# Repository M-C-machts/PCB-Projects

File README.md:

# PCB-Projects
My Personal PCB Projects

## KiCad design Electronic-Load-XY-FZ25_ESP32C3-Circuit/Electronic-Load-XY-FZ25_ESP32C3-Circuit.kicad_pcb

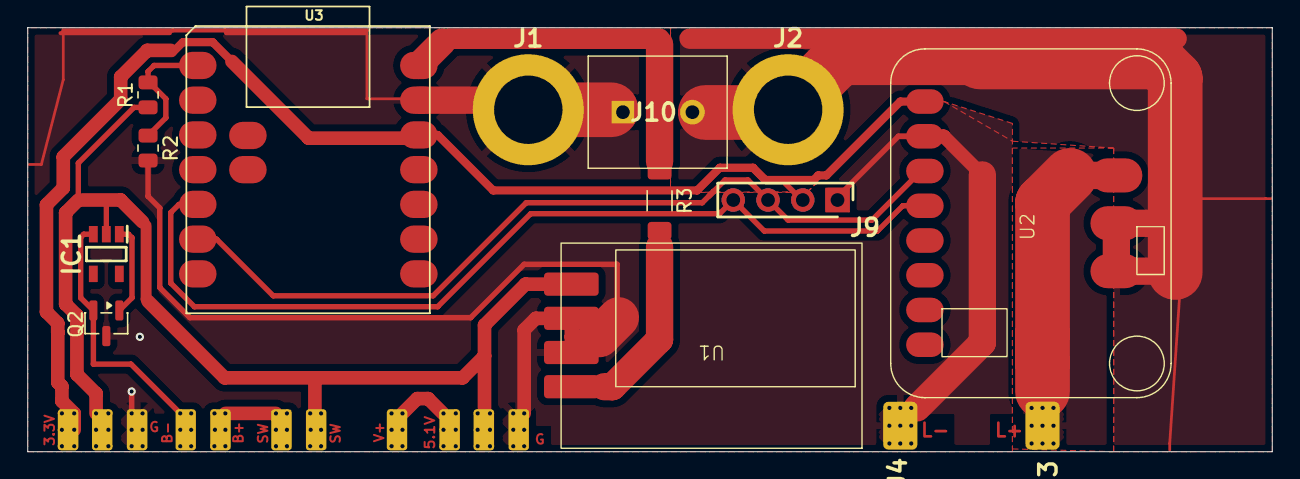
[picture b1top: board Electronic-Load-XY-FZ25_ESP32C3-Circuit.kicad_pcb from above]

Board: 2 copper layers, 91.0 x 31.0 mm, 19 parts (0 on the bottom side), 14 nets.

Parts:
3.3V, 5.1V: Conn_1x3_PH; Mechc.-solder-pad_1x3
B+: Conn_1x2_PH; Mechc.-solder-pad_1x2
IC1: BD5330G; SOT95P280X125-5M
J1, J2: Banana-Socket; banana-socket
J3, J4: mech.-solder-pad_large; Mechc.-solder-pad-large
J8: mech.-solder-pad; Mechc.-solder-pad
J9: Conn_1x4_PH; Conn_1x4_PH_drill dot
J10: Conn_Terminal-Block_1x2
Q2: AO3416; SOT-23
R1, R2: 220k; R_0805_2012Metric
R3: 0R; R_1206_3216Metric_Pad1.30x1.75mm_HandSolder
SW: Conn_1x2_PH; Mechc.-solder-pad_1x2
U1: LiPO-Charge; TP5000-Charge-IC_smal-led
U2: Adafruit INA228; INA228-Footprint
U3: XIAO-ESP32C3; MOUDLE14P-SMD-2.54-21X17.8MM

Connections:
+3.3V: 3.3V.3 (3.3V_out), J9.2 (VDD), U2.1 (VIN), U3.12 (3V3)
+5V: R3.2, U1.1 (IN+)
Banana+: J2.1, J10.2, U2.9 (Vin+), U2.10 (VBus)
GND: 3.3V.1 (GND), 5.1V.1 (GND), J1.1, J4.1, J9.1 (GND), J10.1, Q2.3 (D), R2.2, U1.2 (GND), U1.3 (GND), U2.2 (GND), U3.13 (GND)
L+: J3.1, U2.11 (Vin-)
unnamed: B+.1 (B-), IC1.3 (GND), Q2.2 (S)
unnamed: IC1.1 (VOUT), Q2.1 (G)
unnamed: B+.2 (B+), SW.1
unnamed: 5.1V.3 (5.1V_out), J8.1
unnamed: J9.3 (SCK), U2.3 (SCL), U3.6 (PA9_A5_D5_SCL)
unnamed: J9.4 (SDA), U2.4 (SDA), U3.5 (PA8_A4_D4_SDA)
unnamed: R3.1, U3.14 (5V)
unnamed: R1.2, R2.1, U3.1 (PA02_A0_D0)
V-BATT+: 3.3V.2 (Vbatt), 5.1V.2 (Vbatt), IC1.2 (VDD), R1.1, SW.2, U1.4 (B+)

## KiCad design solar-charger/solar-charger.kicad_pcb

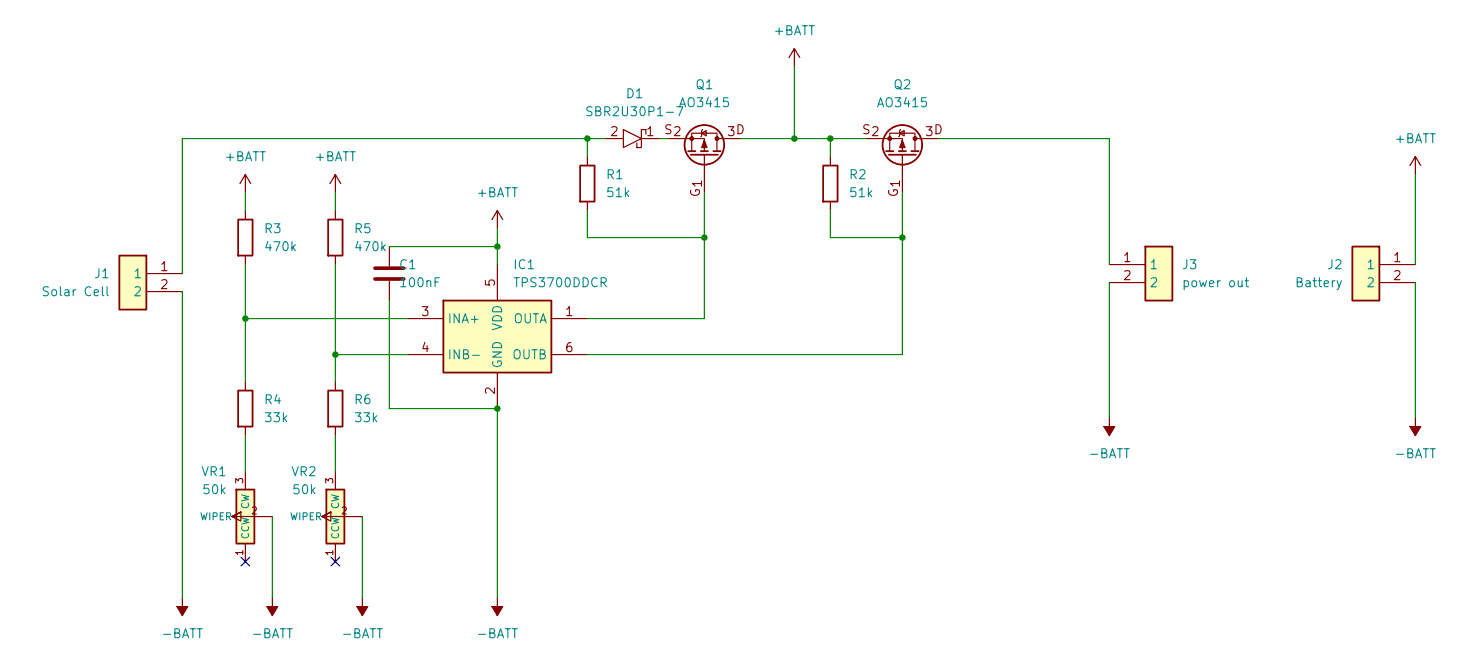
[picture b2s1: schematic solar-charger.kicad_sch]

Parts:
C1: 100nF; C_0805_2012Metric_Pad1.18x1.45mm_HandSolder
D1: SBR2U30P1-7; SODFL3718X100N; Mouser Part Number 621-SBR2U30P1-7
IC1: TPS3700DDCR; SOT98P280X110-6N; Mouser Part Number 595-TPS3700DDCR
J1: Solar Cell; 10129378902001BLF; Manufacturer_Part_Number 10129378-902001BLF
J2: Battery; 10129378902001BLF; Manufacturer_Part_Number 10129378-902001BLF
J3: power out; 10129378902001BLF; Manufacturer_Part_Number 10129378-902001BLF
Q1, Q2: AO3415; SOT-23; Manufacturer_Part_Number AO3415
R1, R2: 51k; R_0805_2012Metric_Pad1.20x1.40mm_HandSolder
R3, R5: 470k; R_0805_2012Metric_Pad1.20x1.40mm_HandSolder
R4, R6: 33k; R_0805_2012Metric_Pad1.20x1.40mm_HandSolder
VR1, VR2: 50k; TC33X2104E; Mouser Part Number 652-TC33X-2-104E

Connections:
+BATT: C1.1, IC1.5 (VDD), J2.1, Q1.3 (D), Q2.2 (S), R2.1, R3.1, R5.1
-BATT: C1.2, IC1.2 (GND), J1.2, J2.2, J3.2, VR1.2 (WIPER), VR2.2 (WIPER)
unnamed: D1.2 (A), J1.1, R1.1
unnamed: D1.1 (K), Q1.2 (S)
unnamed: IC1.3 (INA+), R3.2, R4.1
unnamed: IC1.4 (INB-), R5.2, R6.1
unnamed: IC1.1 (OUTA), Q1.1 (G), R1.2
unnamed: IC1.6 (OUTB), Q2.1 (G), R2.2
unnamed: J3.1, Q2.3 (D)
unnamed: R4.2, VR1.3 (CW)
unnamed: R6.2, VR2.3 (CW)

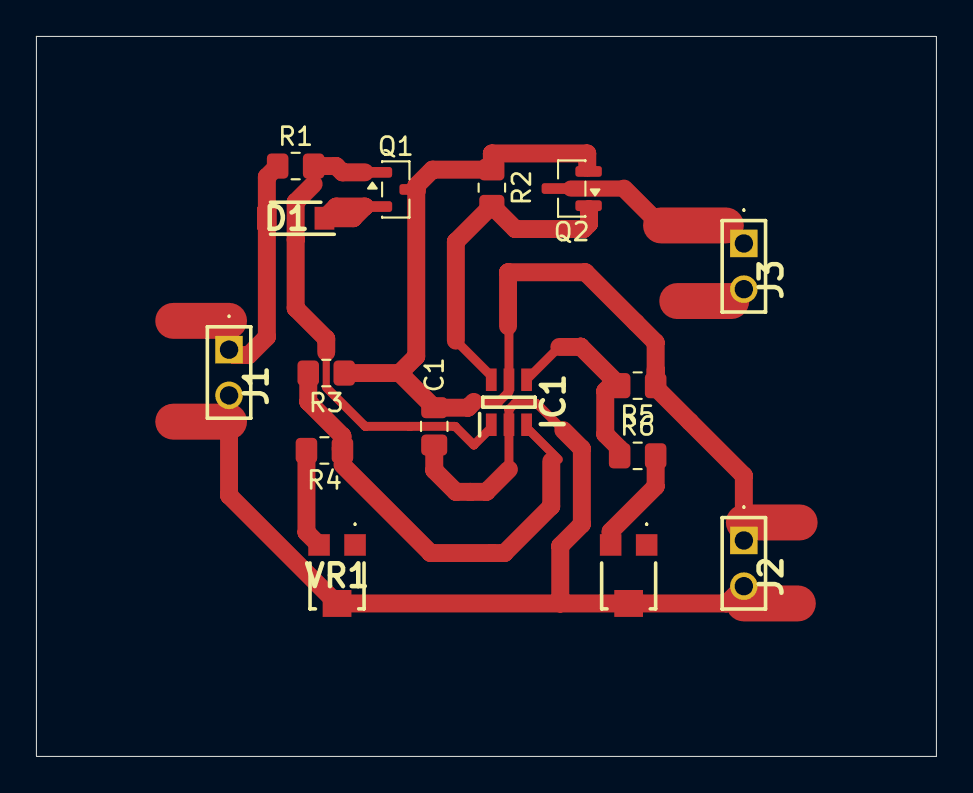
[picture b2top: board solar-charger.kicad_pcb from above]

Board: 2 copper layers, 50.0 x 40.0 mm, 16 parts (0 on the bottom side), 11 nets.

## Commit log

2025-07-22 Add PCB for solar-charger
2025-07-22 Rename
2025-11-21 Add personal part library and update
2025-12-05 Add to part library
2025-12-05 finish 1. working PCB
2025-12-12 Save
2025-12-19 Add working circuit, needs logtime testing
2026-01-20 Add new ICs etc.
2026-01-20 Add first Circuit
2026-01-23 Add, rework parts in own PCB Library
2026-01-23 Add faulty first design
2026-01-26 Rework PCB Library
2026-01-26 Add v2.0 Circuit and footprint
2026-01-27 Update Folder structure
2026-01-27 Add first working firmware
2026-02-04 Rework parts
2026-02-04 Add new project
2026-02-05 Add Working charge section
2026-02-08 Sorted parts
2026-02-08 rewire circuit
2026-02-09 Sort parts into categories
2026-02-19 Rework Partlibrary
2026-02-19 Finish version V1.0
2026-02-19 Add V-A-Meter Project, needs testing
2026-02-21 Move to own repo
2026-02-21 Add Files for home pcb etching
2026-02-21 Move LiFePO4-charge-discharge-board to repo XIAO-LiFePO4-Power-Module
2026-04-06 Add and rework library
2026-04-06 Move V-A-Meter to own repo
